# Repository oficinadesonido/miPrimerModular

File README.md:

# miPrimerModular
Archivos de construcción de módulos del proyecto Mi Primer Modular (My first modular)

Design & code: Daniel Llermaly
Graphic design: Joaquín Contreras
Typeface: contrafonts.cl

www.oficinadesonido.org
https://www.kickstarter.com/projects/oficinadesonido/my-first-modular

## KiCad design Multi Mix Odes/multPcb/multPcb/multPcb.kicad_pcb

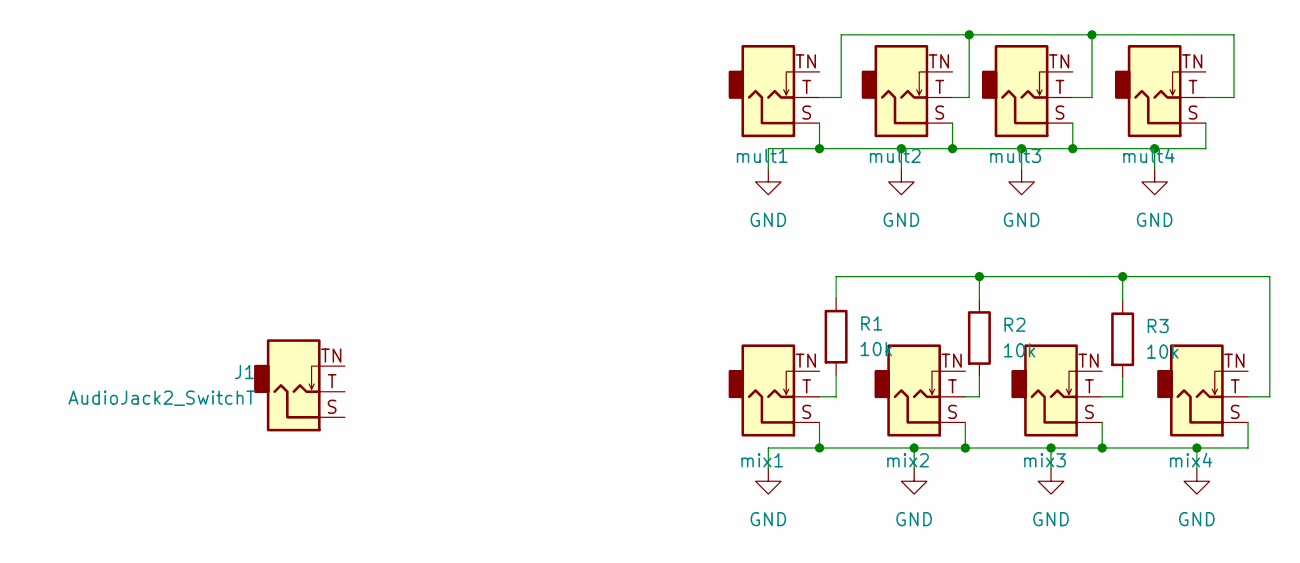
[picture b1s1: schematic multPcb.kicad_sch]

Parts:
J1: AudioJack2_SwitchT
R1, R2, R3: 10k; R_Axial_DIN0204_L3.6mm_D1.6mm_P1.90mm_Vertical
mix1, mix2, mix3, mix4: AudioJack2_Ground; jackEuroTSTN
mult1, mult2, mult3, mult4: AudioJack2_Ground; jackEuroTSTN

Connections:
GND: mix1.S, mix2.S, mix3.S, mix4.S, mult1.S, mult2.S, mult3.S, mult4.S
unnamed: R1.1, R2.1, R3.1, mix4.T
unnamed: R1.2, mix1.T
unnamed: R2.2, mix2.T
unnamed: R3.2, mix3.T
unnamed: mult1.T, mult2.T, mult3.T, mult4.T

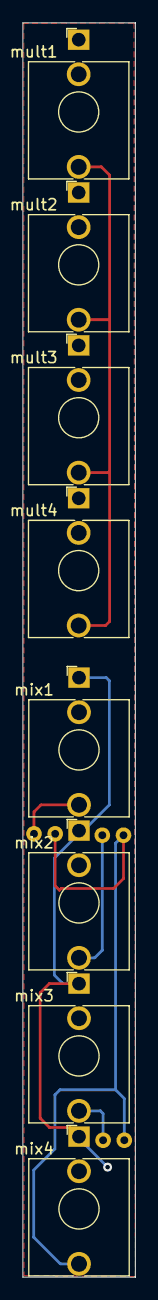
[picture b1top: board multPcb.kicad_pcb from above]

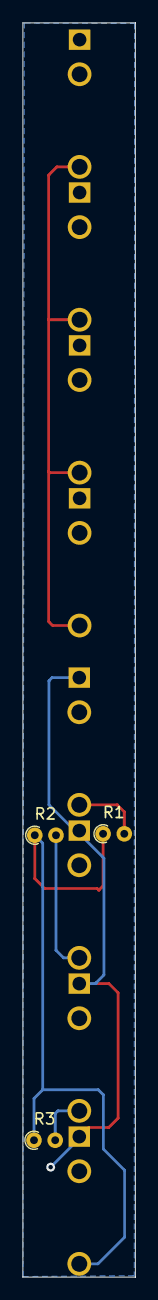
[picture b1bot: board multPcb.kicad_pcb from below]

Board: 2 copper layers, 10.1 x 112.4 mm, 11 parts (3 on the bottom side), 6 nets.

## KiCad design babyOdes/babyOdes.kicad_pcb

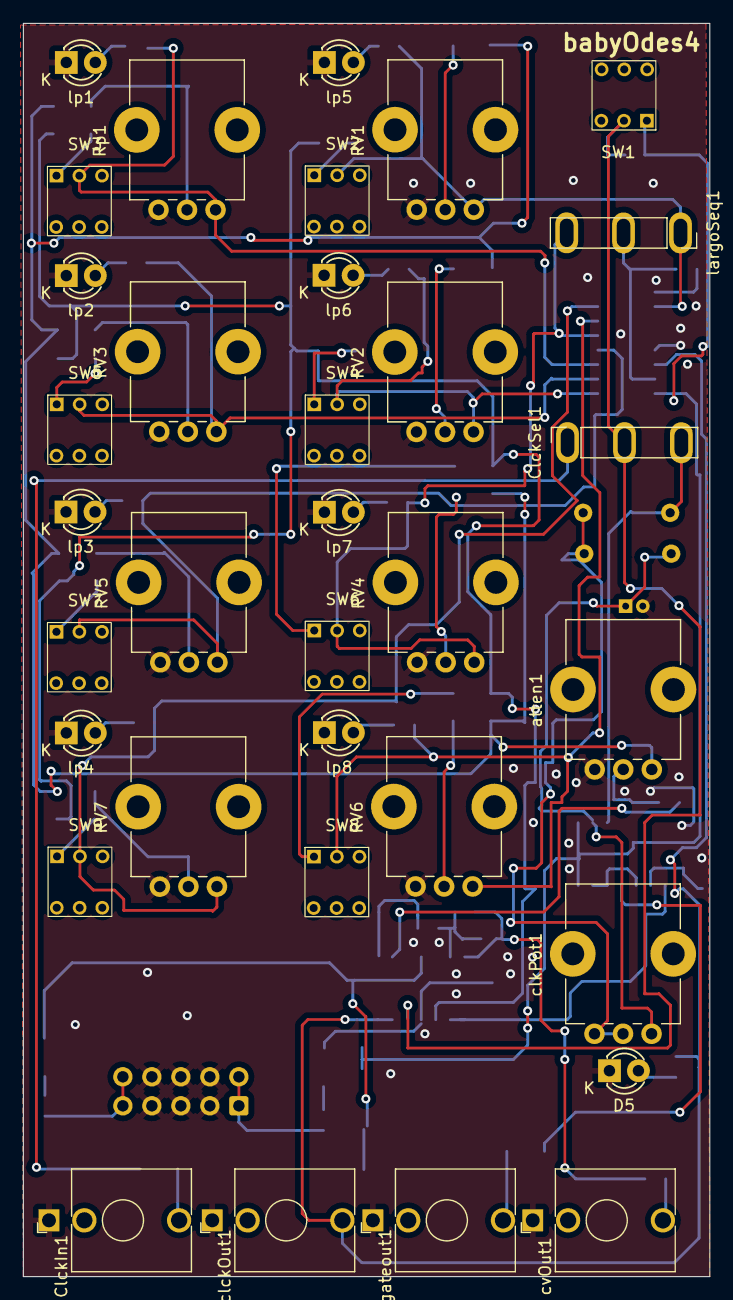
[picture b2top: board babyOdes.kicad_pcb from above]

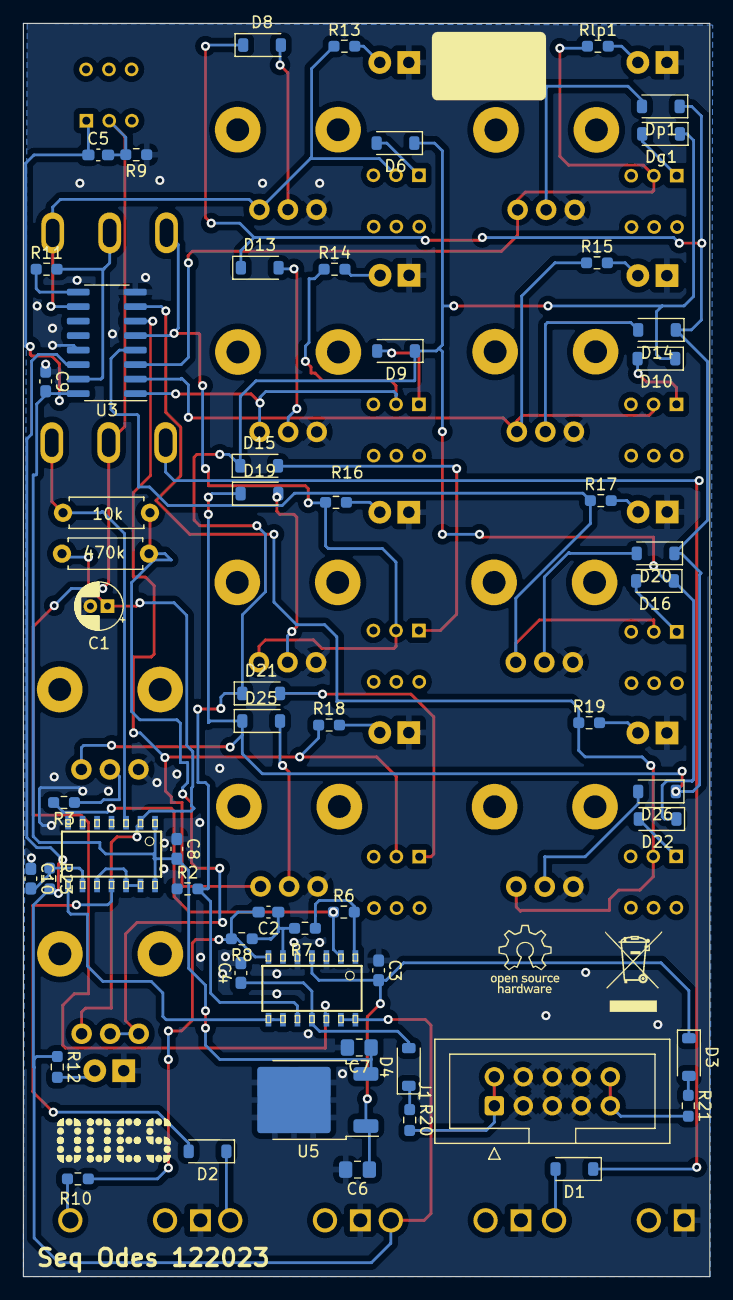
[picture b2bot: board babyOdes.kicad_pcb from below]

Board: 2 copper layers, 60.1 x 109.8 mm, 91 parts (57 on the bottom side), 63 nets.

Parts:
C1: 10uF; CP_Radial_D4.0mm_P1.50mm
C2: 470p; C_0603_1608Metric_Pad1.08x0.95mm_HandSolder
C3, C4, C5, C8, C9: 100nF; C_0603_1608Metric_Pad1.08x0.95mm_HandSolder
C6, C7: 1uF; C_0805_2012Metric_Pad1.18x1.45mm_HandSolder
C10: 0.1uF; C_0603_1608Metric_Pad1.08x0.95mm_HandSolder
ClckIn1: AudioJack2_SwitchT; jack3.5verticalTSTN
ClckSel1: SW_SPDT; colader
D1, D2: D; D_SOD-123
D3, D4, D6, D9, D10, D15, D16, D21, D22: D_Schottky; D_SOD-123
D5: LedClk; LED3mm
D8, D13, D14, D19, D20, D25, D26: 1N4148; D_SOD-123
Dg1: D_Schottky; D_SOD-123
Dp1: 1N4148; D_SOD-123
J1: Conn_02x05_Odd_Even; IDC-Header_2x05_P2.54mm_Vertical
R2, R3, R6, R7, R8, R9, R23: 100k; R_0603_1608Metric_Pad0.98x0.95mm_HandSolder
R4: 10k; R_Axial_DIN0207_L6.3mm_D2.5mm_P7.62mm_Horizontal
R10, R11: 1k; R_0603_1608Metric_Pad0.98x0.95mm_HandSolder
R12, R13, R14, R15, R16, R17, R18, R19: 10k; R_0603_1608Metric_Pad0.98x0.95mm_HandSolder
R20, R21: 10r; R_0603_1608Metric_Pad0.98x0.95mm_HandSolder
R22: 470k; R_Axial_DIN0207_L6.3mm_D2.5mm_P7.62mm_Horizontal
RV1, RV2, RV3, RV4, RV5, RV6, RV7: R_Potentiometer; PotGndPin1
Rlp1: 10k; R_0603_1608Metric_Pad0.98x0.95mm_HandSolder
Rp1: R_Potentiometer; PotGndPin1
SW1: SW_Push; SW_Push_5.8
SW2, SW3, SW4, SW5, SW6, SW7, SW8, SW9: SW_SPST; SW_Push_5.8
U1: HEF4093B; tl074
U2: TL074; tl074
U3: 4017; SOP-16_3.9x9.9mm_P1.27mm
U5: L7805; TO-252-2
atten1: 100k; PotGndPin1
clckOut1: AudioJack2_SwitchT; jack3.5verticalTSTN
clkPot1: 100k; PotGndPin1
cvOut1: AudioJack2_SwitchT; jack3.5verticalTSTN
gateout1: AudioJack2_SwitchT; jack3.5verticalTSTN
largoSeq1: SW_SPDT; colader
lp1, lp2, lp3, lp4, lp5, lp6, lp7, lp8: LED; LED3mm

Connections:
+5V: C5.1, C7.1, C8.2, C9.2, SW1.1, U1.1, U1.14 (VCC), U3.16 (VDD), U5.3 (OUT)
+12V: C3.2, C6.1, D3.1 (K), U2.4 (V+), U5.1 (IN)
-12V: C4.1, D4.2 (A), U2.11 (V-)
CV: D8.1 (K), D13.1 (K), D14.1 (K), D19.1 (K), D20.1 (K), D25.1 (K), D26.1 (K), Dp1.1 (K), atten1.3
GND: C1.2, C3.1, C4.2, C6.2, C7.2, C8.1, C9.1, C10.1, ClckIn1.S, D5.1 (K), J1.3, J1.4, J1.5, J1.6, J1.7, J1.8, R2.1, R9.1, RV1.1, RV2.1, RV3.1, RV4.1, RV5.1, RV6.1, RV7.1, Rp1.1, U1.7 (GND), U2.3 (+), U2.5 (+), U3.8 (VSS), U3.13 (CKEN), U5.2 (GND), atten1.1, clckOut1.S, cvOut1.S, gateout1.S, lp1.1 (K), lp2.1 (K), lp3.1 (K), lp4.1 (K), lp5.1 (K), lp6.1 (K), lp7.1 (K), lp8.1 (K)
Gate: D6.1 (K), D9.1 (K), D10.1 (K), D15.1 (K), D16.1 (K), D21.1 (K), D22.1 (K), Dg1.1 (K), R2.2, U2.10 (+)
unnamed: C1.1, R22.1, U1.2, clkPot1.3
unnamed: C2.2, R8.2, R10.1, U2.7
unnamed: C10.2, R23.1, U1.9
unnamed: ClckSel1.1 (A), D1.1 (K)
unnamed: C5.2, ClckSel1.2 (B), R9.2, SW1.2, U2.12 (+)
unnamed: ClckSel1.3 (C), R4.2, U1.3
unnamed: ClckIn1.T, D1.2 (A)
unnamed: D2.2 (A), U1.11
unnamed: D2.1 (K), gateout1.T
unnamed: D3.2 (A), R21.1
unnamed: D4.1 (K), R20.1
unnamed: D5.2 (A), R12.2
unnamed: D6.2 (A), SW2.1 (A)
unnamed: D8.2 (A), RV1.2
unnamed: D9.2 (A), SW4.1 (A)
unnamed: D10.2 (A), SW5.1 (A)
unnamed: D13.2 (A), RV2.2
unnamed: D14.2 (A), RV3.2
unnamed: D15.2 (A), SW6.1 (A)
unnamed: D16.2 (A), SW7.1 (A)
unnamed: D19.2 (A), RV4.2
unnamed: D20.2 (A), RV5.2
unnamed: D21.2 (A), SW8.1 (A)
unnamed: D22.2 (A), SW9.1 (A)
unnamed: D25.2 (A), RV6.2
unnamed: D26.2 (A), RV7.2
unnamed: Dg1.2 (A), SW3.1 (A)
unnamed: Dp1.2 (A), Rp1.2
unnamed: J1.1, J1.2, R20.2
unnamed: J1.9, J1.10, R21.2
unnamed: R3.1, atten1.2
unnamed: R6.2, R7.1, U2.1
unnamed: R10.2, cvOut1.T
unnamed: R4.1, R22.2, clkPot1.1, clkPot1.2
unnamed: U1.10, U1.12, U1.13
unnamed: R3.2, R6.1, U2.2 (-)
unnamed: C2.1, R7.2, R8.1, U2.6 (-)
unnamed: R11.2, U3.15 (Reset), largoSeq1.2 (B)
unnamed: Rlp1.2, lp1.2 (A)
unnamed: R15.2, lp2.2 (A)
unnamed: R17.2, lp3.2 (A)
unnamed: R19.2, lp4.2 (A)
unnamed: R13.2, lp5.2 (A)
unnamed: R14.2, lp6.2 (A)
unnamed: R16.2, lp7.2 (A)
unnamed: R18.2, lp8.2 (A)
clk: R12.1, R23.2, U2.13 (-), U2.14, U3.14 (CLK), clckOut1.T
gateAmp: U1.8, U2.8, U2.9 (-)
paso0: Rlp1.1, Rp1.3, SW3.2 (B), U3.3 (Q0)
paso1: R15.1, RV3.3, SW5.2 (B), U3.2 (Q1)
paso2: R17.1, RV5.3, SW7.2 (B), U3.4 (Q2)
paso3: R19.1, RV7.3, SW9.2 (B), U3.7 (Q3)
paso4: R13.1, RV1.3, SW2.2 (B), U3.10 (Q4), largoSeq1.1 (A)
paso5: R14.1, RV2.3, SW4.2 (B), U3.1 (Q5)
paso6: R16.1, RV4.3, SW6.2 (B), U3.5 (Q6), largoSeq1.3 (C)
paso7: R18.1, RV6.3, SW8.2 (B), U3.6 (Q7)
paso8: R11.1, U3.9 (Q8)

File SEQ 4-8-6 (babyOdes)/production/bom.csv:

Designator,Footprint,Quantity,Value,LCSC Part #
C1,CP_Radial_D4.0mm_P1.50mm,1,10uF,
C10,0603,1,0.1uF,
C2,0603,1,470p,
"C3, C4, C5, C8, C9",0603,5,100nF,
"C6, C7",0805,2,1uF,
"ClckIn1, clckOut1, cvOut1, gateout1",jack3.5verticalTSTN,4,AudioJack2_SwitchT,
"ClckSel1, largoSeq1",colader,2,SW_SPDT,
"D1, D2",D_SOD-123,2,D,
"D10, D15, D16, D21, D22, D3, D4, D6, D9, Dg1",D_SOD-123,10,D_Schottky,
"D13, D14, D19, D20, D25, D26, D8, Dp1",D_SOD-123,8,1N4148,
D5,LED3mm,1,LedClk,
J1,IDC-Header_2x05_P2.54mm_Vertical,1,Conn_02x05_Odd_Even,
"R10, R11",0603,2,1k,
"R12, R13, R14, R15, R16, R17, R18, R19, Rlp1",0603,9,10k,
"R2, R23, R3, R6, R7, R8, R9",0603,7,100k,
"R20, R21",0603,2,10r,
R22,R_Axial_DIN0207_L6.3mm_D2.5mm_P7.62mm_Horizontal,1,470k,
R4,R_Axial_DIN0207_L6.3mm_D2.5mm_P7.62mm_Horizontal,1,10k,
"RV1, RV2, RV3, RV4, RV5, RV6, RV7, Rp1",PotGndPin1,8,R_Potentiometer,
SW1,SW_Push_5.8,1,SW_Push,
"SW2, SW3, SW4, SW5, SW6, SW7, SW8, SW9",SW_Push_5.8,8,SW_SPST,
U1,tl074,1,HEF4093B,
U2,tl074,1,TL074,
U3,SOP-16_3.9x9.9mm_P1.27mm,1,4017,
U5,TO-252-2,1,L7805,C310413
"atten1, clkPot1",PotGndPin1,2,100k,
"lp1, lp2, lp3, lp4, lp5, lp6, lp7, lp8",LED3mm,8,LED,

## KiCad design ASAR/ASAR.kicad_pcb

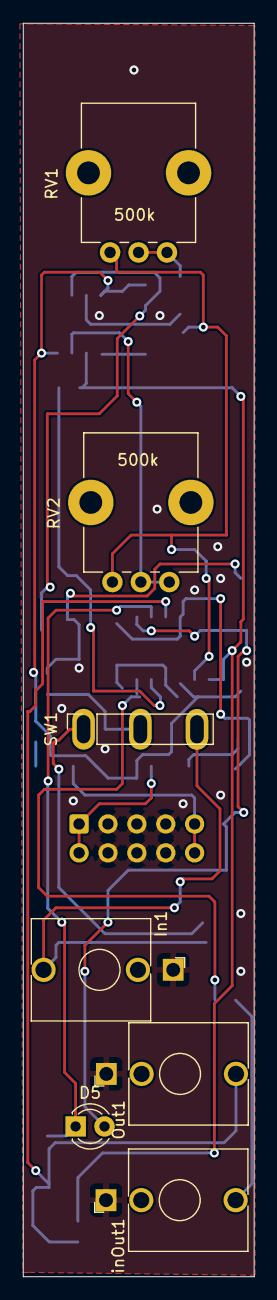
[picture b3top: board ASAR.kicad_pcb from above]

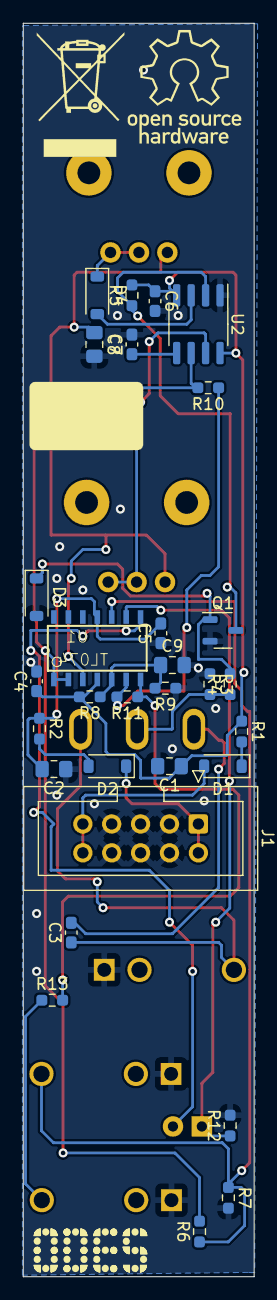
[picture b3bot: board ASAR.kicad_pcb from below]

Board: 2 copper layers, 20.3 x 110.2 mm, 37 parts (30 on the bottom side), 25 nets.

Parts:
C1, C2: 10uF; C_0805_2012Metric_Pad1.18x1.45mm_HandSolder
C3: 100pf; C_0603_1608Metric_Pad1.08x0.95mm_HandSolder
C4, C5, C6: 100nF; C_0603_1608Metric_Pad1.08x0.95mm_HandSolder
C7: 0.01uf; C_0603_1608Metric_Pad1.08x0.95mm_HandSolder
C8: 4.7uF; C_0805_2012Metric_Pad1.18x1.45mm_HandSolder
C9: 1uF; C_0805_2012Metric_Pad1.18x1.45mm_HandSolder
D1, D2: D; D_SOD-123
D3, D4: 1N4148; D_SOD-123
D5: LED; LED_D3.0mm_Clear
In1: Audio-Jack-3; jack3.5vertical
J1: Power Input; IDC-Header_2x05_P2.54mm_Vertical
Out1: Audio-Jack-3; jack3.5vertical
Q1: MMBT3904; SOT-23-3
R1, R2: 10r; R_0603_1608Metric_Pad0.98x0.95mm_HandSolder
R3, R4: 100k; R_0603_1608Metric_Pad0.98x0.95mm_HandSolder
R5, R8, R11: 10k; R_0603_1608Metric_Pad0.98x0.95mm_HandSolder
R6: 2k; R_0603_1608Metric_Pad0.98x0.95mm_HandSolder
R7: 3.3k; R_0603_1608Metric_Pad0.98x0.95mm_HandSolder
R9: 4.7k; R_0603_1608Metric_Pad0.98x0.95mm_HandSolder
R10: 15k; R_0603_1608Metric_Pad0.98x0.95mm_HandSolder
R12, R13: 1k; R_0603_1608Metric_Pad0.98x0.95mm_HandSolder
RV1, RV2: 500k; PotGndPin1
SW1: SW_SPDT; colader
U1: TL074; SOP-14
U2: LM555xN; SOP-8_3.76x4.96mm_P1.27mm
inOut1: Audio-Jack-3; jack3.5vertical

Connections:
+12V: C1.1, C4.1, C6.1, R1.1, R5.2, R8.2, U1.4 (V+), U2.4 (R), U2.8 (VCC)
-12V: C2.2, C5.2, R2.1, U1.11 (V-)
GND: C1.2, C2.1, C4.2, C5.1, C6.2, C7.2, C8.2, C9.2, D3.2 (A), In1.3, J1.3, J1.4, J1.5, J1.6, J1.7, J1.8, Out1.3, Q1.2 (E), R3.1, R7.2, R9.1, R12.2, U2.1 (GND), inOut1.3
unnamed: D1.2 (A), J1.9, J1.10
unnamed: D1.1 (K), R1.2
unnamed: D2.2 (A), R2.2
unnamed: D2.1 (K), J1.1, J1.2
unnamed: D3.1 (K), Q1.1 (B), R4.2
unnamed: D4.2 (A), U2.3 (Q)
unnamed: D4.1 (K), RV1.2, RV1.3
unnamed: D5.2 (A), U1.8
unnamed: D5.1 (K), R12.1, U1.9 (-)
unnamed: Q1.3 (C), R5.1, U2.2 (TR)
unnamed: R11.1, R13.2, U1.7
unnamed: R13.1, inOut1.1
unnamed: C3.2, SW1.1 (A)
unnamed: R3.2, R4.1, SW1.2 (B)
unnamed: C3.1, In1.1, SW1.3 (C)
unnamed: C8.1, RV1.1, RV2.1, U1.3 (+)
unnamed: R6.2, R10.2, U1.1, U1.2 (-), U2.6 (THR)
unnamed: C9.1, R8.1, R9.2, U1.5 (+)
unnamed: R10.1, R11.2, U1.6 (-)
unnamed: Out1.1, R6.1, R7.1, U1.10 (+)
unnamed: C7.1, U2.5 (CV)
unnamed: RV2.2, RV2.3, U2.7 (DIS)

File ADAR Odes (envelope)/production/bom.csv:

Designator,Footprint,Quantity,Value,LCSC Part #
"C1, C2",0805,2,10uF,
C3,0603,1,100pf,
"C4, C5, C6",0603,3,100nF,
C7,0603,1,0.01uf,
C8,0805,1,4.7uF,
C9,0805,1,1uF,
"D1, D2",D_SOD-123,2,D,
"D3, D4",D_SOD-123,2,1N4148,
D5,LED_D3.0mm_Clear,1,LED,
"In1, Out1, inOut1",jack3.5vertical,3,Audio-Jack-3,
J1,IDC-Header_2x05_P2.54mm_Vertical,1,Power Input,
Q1,SOT-23-3,1,MMBT3904,
"R1, R2",0603,2,10r,
R10,0603,1,15k,
"R11, R5, R8",0603,3,10k,
"R12, R13",0603,2,1k,
"R3, R4",0603,2,100k,
R6,0603,1,2k,
R7,0603,1,3.3k,
R9,0603,1,4.7k,
"RV1, RV2",PotGndPin1,2,500k,
SW1,colader,1,SW_SPDT,
U1,SOP-14,1,TL074,
U2,SOP-8_3.76x4.96mm_P1.27mm,1,LM555xN,

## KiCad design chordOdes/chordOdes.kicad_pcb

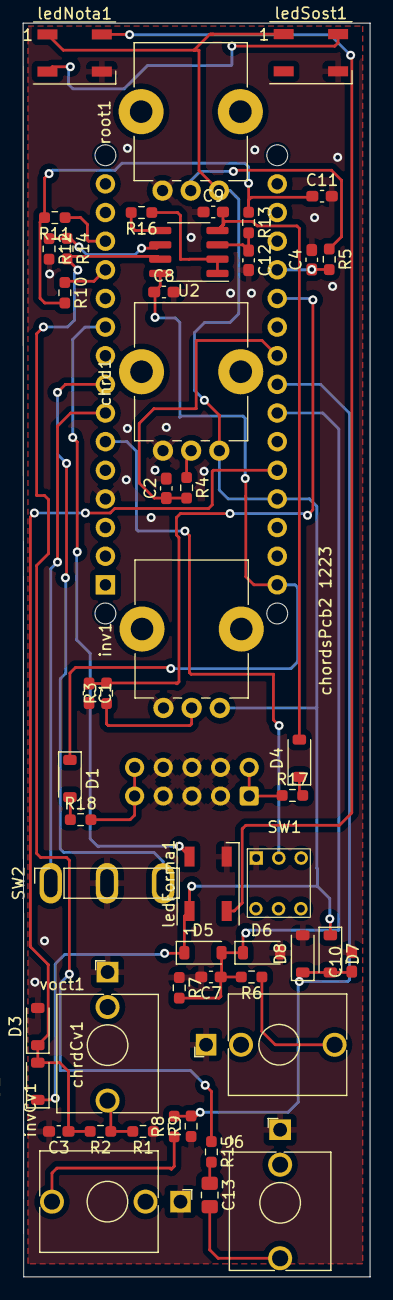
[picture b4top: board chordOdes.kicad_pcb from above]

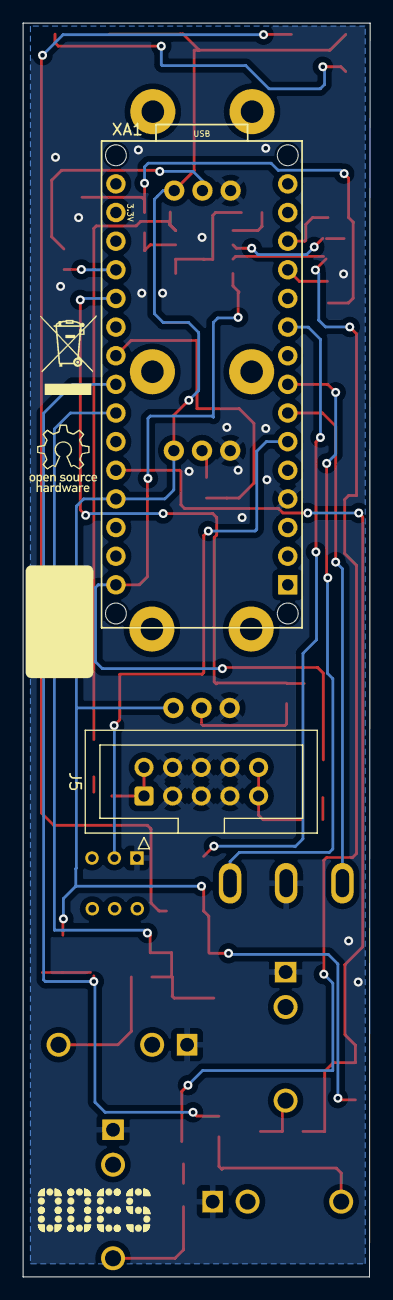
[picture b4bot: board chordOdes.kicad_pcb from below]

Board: 2 copper layers, 30.8 x 111.2 mm, 52 parts (2 on the bottom side), 36 nets.

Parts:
C1, C2, C4, C8, C9, C12: 10nF; C_0603_1608Metric_Pad1.08x0.95mm_HandSolder
C3, C7, C10: 68nF; C_0603_1608Metric_Pad1.08x0.95mm_HandSolder
C11: 4.7nF; C_0603_1608Metric_Pad1.08x0.95mm_HandSolder
C13: 4.7uF; C_0805_2012Metric_Pad1.18x1.45mm_HandSolder
D1, D4: D; D_SOD-123
D2, D3, D5, D6, D7, D8: D_Schottky; D_SOD-123
J5: Conn_02x05_Odd_Even; IDC-Header_2x05_P2.54mm_Vertical
J6: AudioJack2_Ground; jackEuroTSTN
R1, R7, R9: 100k; R_0603_1608Metric_Pad0.98x0.95mm_HandSolder
R2: 100r; R_0603_1608Metric_Pad0.98x0.95mm_HandSolder
R3, R4, R5, R6, R8, R12, R14, R16: 1k; R_0603_1608Metric_Pad0.98x0.95mm_HandSolder
R10, R13: 3.9k; R_0603_1608Metric_Pad0.98x0.95mm_HandSolder
R11: 499k; R_0603_1608Metric_Pad0.98x0.95mm_HandSolder
R15: 220r; R_0603_1608Metric_Pad0.98x0.95mm_HandSolder
R17, R18: 10r; R_0603_1608Metric_Pad0.98x0.95mm_HandSolder
SW1: SW_Push; SW_Push_5.8
SW2: SW_SPDT; colader
U2: TL072; SOP-8_3.76x4.96mm_P1.27mm
XA1: Arduino_Nano_Socket
chrd1: R_Potentiometer; PotGndPin1
chrdCv1: AudioJack2_Ground; jackEuroTSTN
inv1: R_Potentiometer; PotGndPin1
invCv1: AudioJack2_Ground; jackEuroTSTN
ledForma1: NeoPixel_THT; LED_WS2812B
ledNota1: NeoPixel_THT; LED_WS2812B
ledSost1: NeoPixel_THT; LED_WS2812B
root1: R_Potentiometer; PotGndPin1
voct1: AudioJack2_Ground; jackEuroTSTN

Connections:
+5V: D2.1 (K), D5.1 (K), D7.1 (K), XA1.5V, chrd1.3, inv1.3, ledForma1.3 (VDD), ledNota1.3 (VDD), ledSost1.3 (VDD), root1.3
-12V: C9.2, D4.2 (A), U2.4 (V-)
GND: C1.2, C2.2, C3.2, C4.2, C7.2, C8.2, C9.1, C10.2, C11.2, C12.2, D3.2 (A), D6.2 (A), D8.2 (A), J5.3, J5.4, J5.5, J5.6, J5.7, J5.8, J6.G, R1.1, R7.1, R9.1, R12.2, SW1.1, SW2.2 (B), XA1.GND1 (GND), chrd1.1, chrdCv1.G, inv1.1, invCv1.G, ledForma1.2 (GND), ledNota1.2 (GND), ledSost1.2 (GND), root1.1, voct1.G
unnamed: C11.1, R10.2, R11.2, R13.1
unnamed: C13.1, R15.2
unnamed: D1.2 (A), R18.1
unnamed: D4.1 (K), R17.2
unnamed: J5.1, J5.2, R17.1
unnamed: J5.9, J5.10, R18.2
unnamed: R1.2, R2.1, voct1.T
unnamed: R3.1, inv1.2
unnamed: R4.1, chrd1.2
unnamed: R5.1, root1.2
unnamed: R6.1, chrdCv1.T
unnamed: R8.1, invCv1.T
unnamed: R10.1, XA1.D9
unnamed: R14.2, R15.1, U2.7
unnamed: R16.1, U2.1, U2.2 (-)
unnamed: R16.2, U2.5 (+)
unnamed: R12.1, R14.1, U2.6 (-)
unnamed: R11.1, XA1.D10 (D10_CS)
unnamed: ledForma1.1 (DOUT), ledNota1.4 (DIN)
unnamed: ledNota1.1 (DOUT), ledSost1.4 (DIN)
btnFrm: SW1.2, XA1.D3 (D3_INT1)
chrd: C2.1, R4.2, XA1.A3
chrdCv: C7.1, D5.2 (A), D6.1 (K), R6.2, R7.2, XA1.A5 (A5_SCL)
inv: C1.1, R3.2, XA1.A1
invCv: C10.1, D7.2 (A), D8.1 (K), R8.2, R9.2, XA1.A4 (A4_SDA)
led: XA1.D7, ledForma1.4 (DIN)
modeSw1: SW2.1 (A), XA1.D4
modeSw2: SW2.3 (C), XA1.D5
out: C13.2, J6.T
preOut: C12.1, R13.2, U2.3 (+)
root: C4.1, R5.2, XA1.A0
vin: C8.1, D1.1 (K), U2.8 (V+), XA1.VIN
voct: C3.1, D2.2 (A), D3.1 (K), R2.2, XA1.A7

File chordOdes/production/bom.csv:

Designator,Footprint,Quantity,Value,LCSC Part #
"C1, C12, C2, C4, C8, C9",0603,6,10nF,
"C10, C3, C7",0603,3,68nF,
C11,0603,1,4.7nF,
C13,0805,1,4.7uF,
"D1, D4",D_SOD-123,2,D,
"D2, D3, D5, D6, D7, D8",D_SOD-123,6,D_Schottky,
J5,IDC-Header_2x05_P2.54mm_Vertical,1,Conn_02x05_Odd_Even,
"J6, chrdCv1, invCv1, voct1",jackEuroTSTN,4,AudioJack2_Ground,
"R1, R7, R9",0603,3,100k,
"R10, R13",0603,2,3.9k,
R11,0603,1,499k,
"R12, R14, R16, R3, R4, R5, R6, R8",0603,8,1k,
R15,0603,1,220r,
"R17, R18",0603,2,10r,
R2,0603,1,100r,
SW1,SW_Push_5.8,1,SW_Push,
SW2,colader,1,SW_SPDT,
U2,SOP-8_3.76x4.96mm_P1.27mm,1,TL072,
XA1,Arduino_Nano_Socket,1,Arduino_Nano_Socket,
"chrd1, inv1, root1",PotGndPin1,3,R_Potentiometer,
"ledForma1, ledNota1, ledSost1",LED_WS2812B,3,NeoPixel_THT,

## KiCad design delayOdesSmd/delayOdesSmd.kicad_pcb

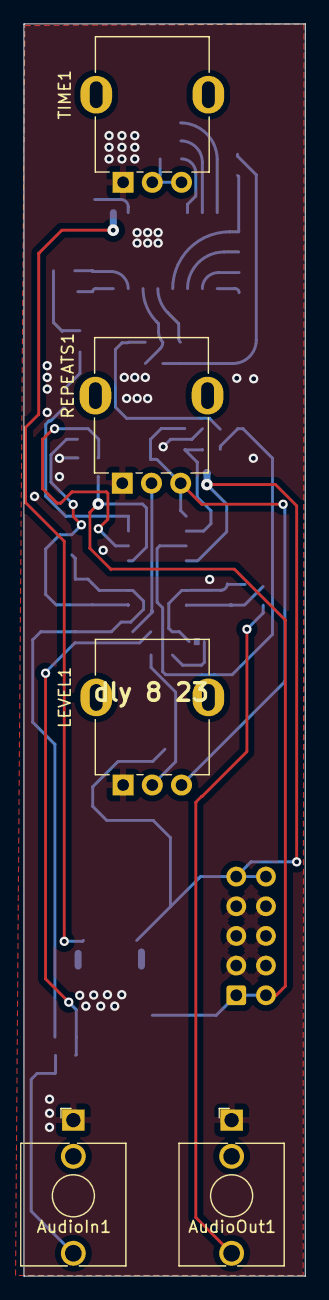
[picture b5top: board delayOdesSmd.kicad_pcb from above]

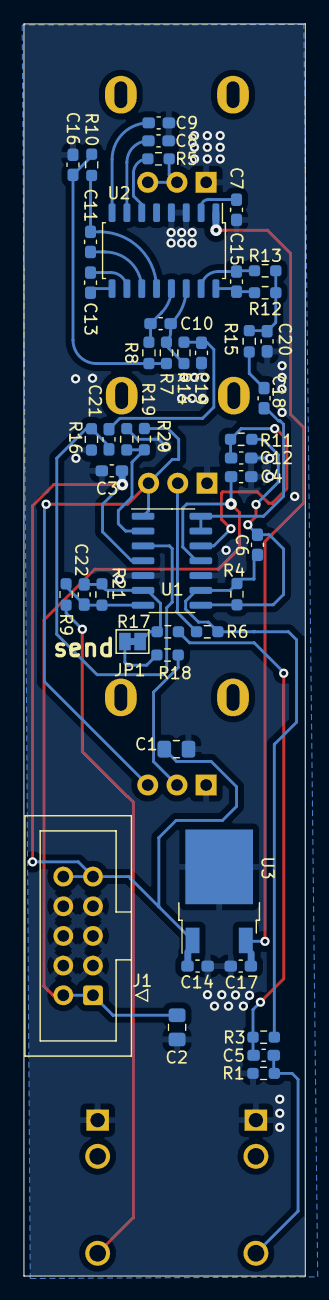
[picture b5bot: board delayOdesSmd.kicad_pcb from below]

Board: 2 copper layers, 24.1 x 107.2 mm, 52 parts (47 on the bottom side), 36 nets.

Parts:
AudioIn1: AudioJack2_SwitchT; AudioJack_3.5mm
AudioOut1: AudioJack2_SwitchT; AudioJack_3.5mm
C1, C2: 22uF; C_0805_2012Metric_Pad1.18x1.45mm_HandSolder
C3, C4, C8, C9, C11, C13, C17: 100nF; C_0603_1608Metric_Pad1.08x0.95mm_HandSolder
C5: 220nF; C_0603_1608Metric_Pad1.08x0.95mm_HandSolder
C6: 47pF; C_0603_1608Metric_Pad1.08x0.95mm_HandSolder
C7, C18: 1uF; C_0603_1608Metric_Pad1.08x0.95mm_HandSolder
C10, C12, C15, C19: 2.2nF; C_0603_1608Metric_Pad1.08x0.95mm_HandSolder
C14: 330nF; C_0603_1608Metric_Pad1.08x0.95mm_HandSolder
C16: 15nF; C_0603_1608Metric_Pad1.08x0.95mm_HandSolder
C20: 4.7nF; C_0603_1608Metric_Pad1.08x0.95mm_HandSolder
C21: 10nF; C_0603_1608Metric_Pad1.08x0.95mm_HandSolder
C22: 68pF; C_0603_1608Metric_Pad1.08x0.95mm_HandSolder
J1: IDC_2x05; IDC-Header_2x05_P2.54mm_Vertical
JP1: Jumper_2_Bridged; SolderJumper-2_P1.3mm_Bridged_Pad1.0x1.5mm
LEVEL1: B10k; Potentiometer_RV09
R1, R16: 1M; R_0603_1608Metric_Pad0.98x0.95mm_HandSolder
R3, R6, R17, R20, R21: 100k; R_0603_1608Metric_Pad0.98x0.95mm_HandSolder
R4, R8, R10, R11, R12, R13, R14, R15: 10k; R_0603_1608Metric_Pad0.98x0.95mm_HandSolder
R5: 2.7k; R_0603_1608Metric_Pad0.98x0.95mm_HandSolder
R7, R19: 20k; R_0603_1608Metric_Pad0.98x0.95mm_HandSolder
R9: 1k; R_0603_1608Metric_Pad0.98x0.95mm_HandSolder
R18: 68k; R_0603_1608Metric_Pad0.98x0.95mm_HandSolder
REPEATS1: B10k; Potentiometer_RV09
TIME1: B100k; Potentiometer_RV09
U1: TL074; SOIC-14_3.9x8.7mm_P1.27mm
U2: PT2399; SOP-16_4.55x10.3mm_P1.27mm
U3: L7805; TO-252-2

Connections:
+5V: C17.1, U2.1 (VCC), U3.3 (OUT)
+12V: C1.1, C3.1, C14.1, J1.9, J1.10, U1.4 (V+), U3.1 (IN)
-12V: C2.2, C4.2, J1.1, J1.2, U1.11 (V-)
DRY_OUT: C5.1, R3.1, R17.1
GND: AudioIn1.S, AudioOut1.S, C1.2, C2.1, C3.2, C4.1, C7.2, C8.1, C9.1, C12.1, C14.2, C16.1, C17.2, C19.1, C20.2, J1.3, J1.4, J1.5, J1.6, J1.7, J1.8, LEVEL1.1, R1.1, R16.1, R19.1, REPEATS1.1, TIME1.1, U1.5 (+), U1.10 (+), U2.3 (AGND), U2.4 (DGND), U3.2 (GND)
unnamed: AudioIn1.T, C5.2, R1.2
unnamed: AudioOut1.T, R9.1
unnamed: C6.1, R4.2, R11.1, U1.8
unnamed: C16.2, R7.1, R8.1, R10.1
unnamed: C18.1, R15.1
unnamed: C19.2, C21.1, R14.1
unnamed: C20.1, R12.1, R13.1, R15.2
unnamed: C22.1, R9.2, R21.2, U1.7
unnamed: JP1.1 (A), R18.2
unnamed: C22.2, JP1.2 (B), R17.2, R21.1, U1.6 (-)
unnamed: LEVEL1.3, R20.2, REPEATS1.3, U1.1
unnamed: R5.2, TIME1.2, TIME1.3
unnamed: C21.2, R16.2, U1.3 (+)
unnamed: R19.2, R20.1, U1.2 (-)
unnamed: C6.2, R3.2, R4.1, R6.2, U1.9 (-)
unnamed: C12.2, R11.2, U1.12 (+)
unnamed: C18.2, U1.13 (-), U1.14
unnamed: C9.2, U2.8 (CC0)
unnamed: C8.2, U2.7 (CC1)
unnamed: C15.2, R12.2, U2.16 (LPF1-IN)
unnamed: C15.1, R13.2, U2.15 (LPF1-OUT)
unnamed: C10.1, R8.2, U2.13 (LPF2-IN)
unnamed: C10.2, R7.2, R14.2, U2.14 (LPF2-OUT)
unnamed: C13.2, U2.10 (OP1-IN)
unnamed: C13.1, U2.9 (OP1-OUT)
unnamed: C11.1, U2.11 (OP2-IN)
unnamed: C11.2, R10.2, U2.12 (OP2-OUT)
unnamed: C7.1, U2.2 (REF)
unnamed: R5.1, U2.6 (VCO)
REPEATS: R6.1, REPEATS1.2
WET_OUT: LEVEL1.2, R18.1

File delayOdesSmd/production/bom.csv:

Designator,Footprint,Quantity,Value,LCSC Part #
"AudioIn1, AudioOut1",AudioJack_3.5mm,2,AudioJack2_SwitchT,
"C1, C2",0805,2,22uF,C49678
"C10, C12, C15, C19",0603,4,2.2nF,C107043
"C11, C13, C17, C3, C4, C8, C9",0603,7,100nF,C91183
C14,0603,1,330nF,C107070
C16,0603,1,15nF,C2210963
"C18, C7",0603,2,1uF,C105174
C20,0603,1,4.7nF,C115060
C21,0603,1,10nF,C115056
C22,0603,1,68pF,C519457
C5,0603,1,220nF,C97857
C6,0603,1,47pF,C105622
"D2, D3",D_SOD-123,2,1N4001,
J1,IDC-Header_2x05_P2.54mm_Vertical,1,IDC_2x05,C706914
JP1,SolderJumper-2_P1.3mm_Bridged_Pad1.0x1.5mm,1,Jumper_2_Bridged,
"LEVEL1, REPEATS1",Potentiometer_RV09,2,B10k,
"R1, R16",0603,2,1M,C105578
"R10, R11, R12, R13, R14, R15, R4, R8",0603,8,10k,C116677
"R17, R20, R21, R3, R6",0603,5,100k,C14675
R18,0603,1,68k,C114633
"R19, R7",0603,2,20k,C105575
"R22, R23",0603,2,10r,C116677
R5,0603,1,2.7k,C114612
R9,0603,1,1k,C22548
TIME1,Potentiometer_RV09,1,B100k,
U1,SOIC-14_3.9x8.7mm_P1.27mm,1,TL074,C107644
U2,SOP-16_4.55x10.3mm_P1.27mm,1,PT2399,C126407
U3,TO-252-2,1,L7805,C310413

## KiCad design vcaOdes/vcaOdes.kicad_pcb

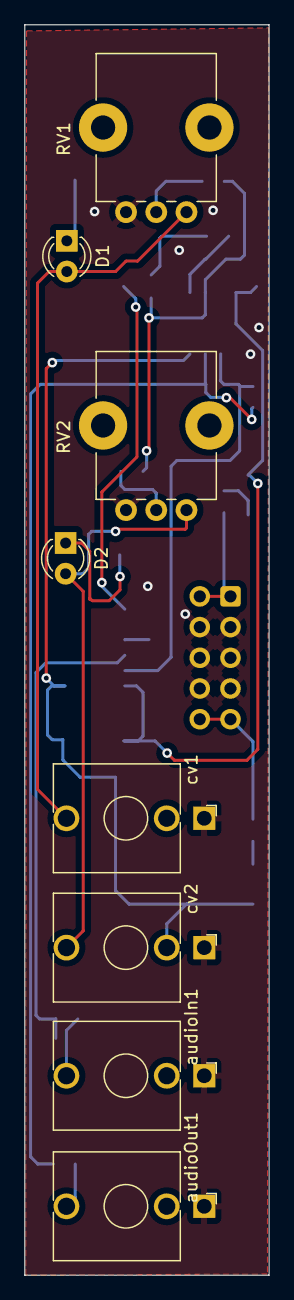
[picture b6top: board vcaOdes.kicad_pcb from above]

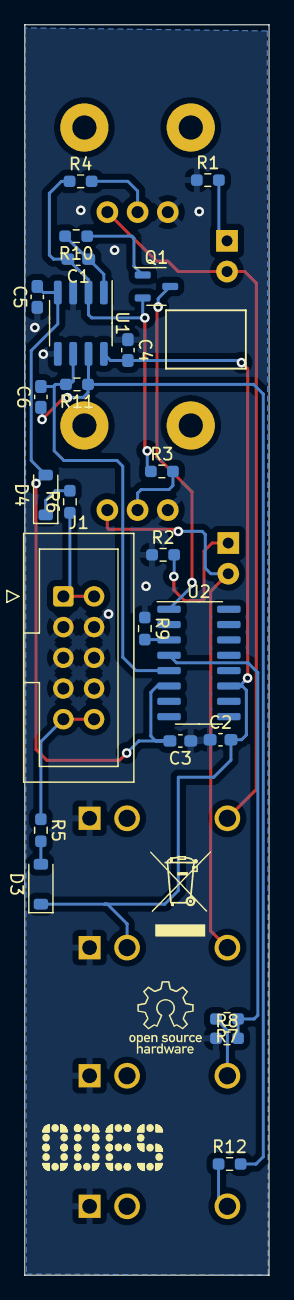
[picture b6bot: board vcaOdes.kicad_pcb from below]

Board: 2 copper layers, 20.2 x 103.4 mm, 32 parts (24 on the bottom side), 23 nets.

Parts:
C1, C6: 120pF; C_0603_1608Metric_Pad1.08x0.95mm_HandSolder
C2, C3, C4, C5: 100nF; C_0603_1608Metric_Pad1.08x0.95mm_HandSolder
D1, D2: LED; LED_D3.0mm
D3, D4: 1N4001; D_SOD-123
J1: Conn_02x05_Odd_Even; IDC-Header_2x05_P2.54mm_Vertical
Q1: BC559; SOT-23-BEC
R1, R2: 10k; R_0603_1608Metric_Pad0.98x0.95mm_HandSolder
R3, R4, R7, R10: 20k; R_0603_1608Metric_Pad0.98x0.95mm_HandSolder
R5, R6: 10r; R_0603_1608Metric_Pad0.98x0.95mm_HandSolder
R8, R9: 100; R_0603_1608Metric_Pad0.98x0.95mm_HandSolder
R11: 47k; R_0603_1608Metric_Pad0.98x0.95mm_HandSolder
R12: 680; R_0603_1608Metric_Pad0.98x0.95mm_HandSolder
RV1, RV2: 100k; Pot-bourns-alpha
U1: TL072; SOP-8_3.76x4.96mm_P1.27mm
U2: LM13700; SOIC-16_3.9x9.9mm_P1.27mm
audioIn1: AudioJack2_SwitchT; jackEuroTSTN
audioOut1: AudioJack2_SwitchT; jackEuroTSTN
cv1, cv2: AudioJack2_SwitchT; jackEuroTSTN

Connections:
+12V: C2.2, C4.2, D3.1 (K), U1.8 (V+), U2.11 (V+), cv2.TN
-12V: C3.2, C5.2, D4.2 (A), U1.4 (V-), U2.6 (V-)
GND: C2.1, C3.1, C4.1, C5.1, J1.3, J1.4, J1.5, J1.6, J1.7, J1.8, R1.1, R2.1, R8.1, R9.1, RV1.3, RV2.3, U1.3 (+), U1.5 (+), audioIn1.S, audioOut1.S, cv1.S, cv2.S
unnamed: C1.1, R10.2, U1.1
unnamed: C6.1, R11.1, R12.2, U1.7
unnamed: D1.2 (A), RV1.1, cv1.T
unnamed: D1.1 (K), R1.2
unnamed: D2.2 (A), RV2.1, cv2.T
unnamed: D2.1 (K), R2.2
unnamed: D3.2 (A), R5.2
unnamed: D4.1 (K), R6.2
unnamed: J1.1, J1.2, R6.1
unnamed: J1.9, J1.10, R5.1
unnamed: Q1.2 (B), R10.1
unnamed: Q1.1 (C), U2.1
unnamed: C1.2, Q1.3 (E), R3.1, R4.1, U1.2 (-)
unnamed: R3.2, RV2.2
unnamed: R4.2, RV1.2
unnamed: R7.2, audioIn1.T
unnamed: R12.1, audioOut1.T
unnamed: C6.2, R11.2, U1.6 (-), U2.5
unnamed: R9.2, U2.3 (+)
unnamed: R7.1, R8.2, U2.4 (-)

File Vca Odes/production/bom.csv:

Designator,Footprint,Quantity,Value,LCSC Part #
"C1, C6",0603,2,120pF,
"C2, C3, C4, C5",0603,4,100nF,
"D1, D2",LED_D3.0mm,2,LED,
"D3, D4",D_SOD-123,2,1N4001,
J1,IDC-Header_2x05_P2.54mm_Vertical,1,Conn_02x05_Odd_Even,
Q1,SOT-23-BEC,1,BC559,
"R1, R2",0603,2,10k,
"R10, R3, R4, R7",0603,4,20k,
R11,0603,1,47k,
R12,0603,1,680,
"R5, R6",0603,2,10r,
"R8, R9",0603,2,100,
"RV1, RV2",Pot-bourns-alpha,2,100k,
U1,SOP-8_3.76x4.96mm_P1.27mm,1,TL072,
U2,SOIC-16_3.9x9.9mm_P1.27mm,1,LM13700,
"audioIn1, audioOut1, cv1, cv2",jackEuroTSTN,4,AudioJack2_SwitchT,

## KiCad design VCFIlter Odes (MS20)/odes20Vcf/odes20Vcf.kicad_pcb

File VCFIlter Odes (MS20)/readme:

This is an VCF Low Pass and Hi Pass Filter MS-20 style. Part of the My First Modular Project by http://oficinadesonido.org

Adaptation made by Daniel Llermaly
Art Panel by @jkocontreras

Based on Simple ms20_vcf Arthur Saunier (https://github.com/arthursaunier/Synth/tree/main/ms20_vcf/simple)
which is based on Michael Barton's work (https://www.bartonmusicalcircuits.com/synthstuff.html#analog)

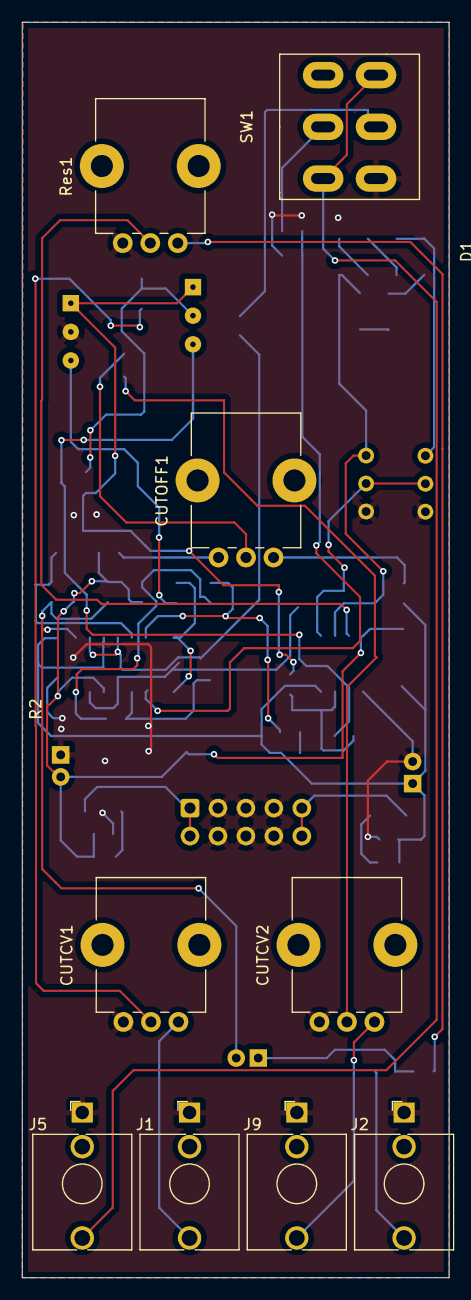
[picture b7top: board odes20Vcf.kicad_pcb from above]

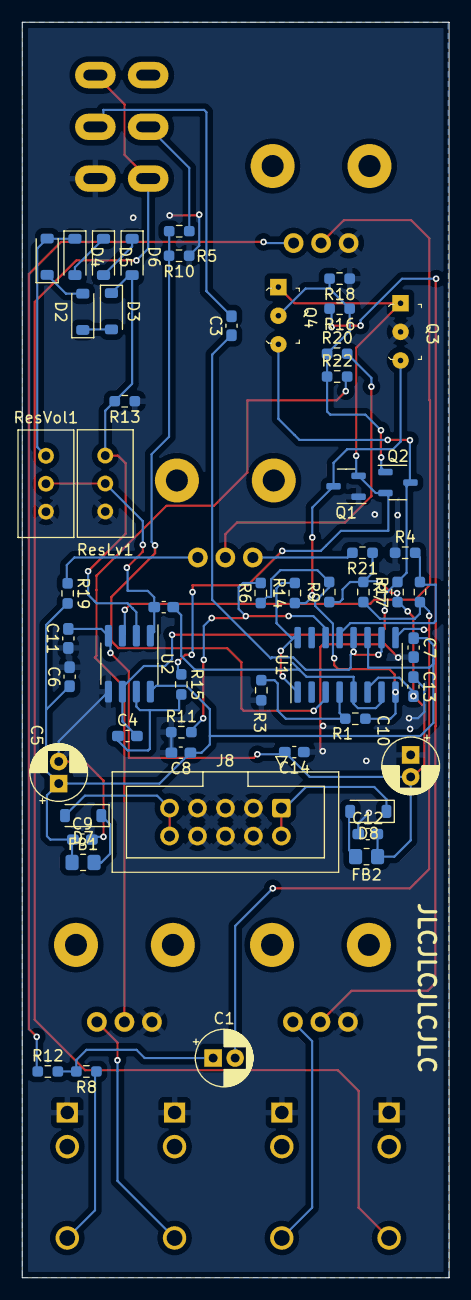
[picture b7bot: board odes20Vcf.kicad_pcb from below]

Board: 2 copper layers, 38.8 x 114.1 mm, 64 parts (55 on the bottom side), 42 nets.

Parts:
C1, C5, C10: 10uF; CP_Radial_D5.0mm_P2.00mm
C2, C3, C4: 1nF; C_0603_1608Metric_Pad1.08x0.95mm_HandSolder
C6, C7, C8, C9, C11, C12, C13, C14: 100nF; C_0603_1608Metric_Pad1.08x0.95mm_HandSolder
CUTCV1, CUTCV2: 100k; Pot-bourns-alpha
CUTOFF1: 100k; Pot-bourns-alpha
D1, D2, D3, D4, D5, D6: 1N4148; D_SOD-123
D7, D8: D; D_SOD-123
FB1, FB2: 10R; R_0805_2012Metric_Pad1.20x1.40mm_HandSolder
J1, J9: FilterCV1; Thonkiconn
J2: FilterOut1; Thonkiconn
J5: FilterIn1; Thonkiconn
J8: Power Input; IDC-Header_2x05_P2.54mm_Vertical
Q1, Q2: BC559; SOT-23-BEC
Q3, Q4: BC559; BC548tht
R1, R2, R5, R6, R17, R20: 100k; R_0603_1608Metric_Pad0.98x0.95mm_HandSolder
R3, R4, R10, R11: 470; R_0603_1608Metric_Pad0.98x0.95mm_HandSolder
R7, R9: 1.8k; R_0603_1608Metric_Pad0.98x0.95mm_HandSolder
R8, R12, R15: 1k; R_0603_1608Metric_Pad0.98x0.95mm_HandSolder
R13, R14, R18: 2.2k; R_0603_1608Metric_Pad0.98x0.95mm_HandSolder
R16, R22: 82k; R_0603_1608Metric_Pad0.98x0.95mm_HandSolder
R19: 33k; R_0603_1608Metric_Pad0.98x0.95mm_HandSolder
R21: 56k; R_0603_1608Metric_Pad0.98x0.95mm_HandSolder
Res1: 100k; Pot-bourns-alpha
ResLv1: 10k; Potentiometer_Bourns_3386C_Horizontal
ResVol1: 10k; Potentiometer_Bourns_3386C_Horizontal
SW1: Hpass/Lpass Switch; SW_DPDT_Toggle
U1: LM13700; SOIC-16_3.9x9.9mm_P1.27mm
U2: TL072; SOP-8_3.76x4.96mm_P1.27mm

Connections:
+12V: C5.1, C6.1, C7.1, C8.1, C9.1, FB1.1, R19.2, U1.11 (V+), U2.8 (V+)
-12V: C10.2, C11.2, C12.2, C13.2, C14.2, FB2.1, R7.1, R9.1, R17.1, R21.1, U1.6 (V-), U2.4 (V-)
/CVIn: CUTCV1.1, J1.T
/CVIn2: CUTCV2.1, J9.T
/Cutoff: Q2.2 (B), Q4.2 (B), R16.1, R18.2, R20.1, R22.1
/FilterIn: J5.T, SW1.3 (C), SW1.4 (A)
/FilterOut: J2.T, R8.1
/HPass: C3.2, SW1.5 (B)
/LPass: R5.1, SW1.2 (B)
/Out1: C1.1, R8.2, R12.2
/ResOut: Res1.2, U2.3 (+)
GND: C5.2, C6.2, C7.2, C8.2, C9.2, C10.1, C11.1, C12.1, C13.1, C14.1, CUTCV1.3, CUTCV2.3, J1.S, J2.S, J5.S, J8.3, J8.4, J8.5, J8.6, J8.7, J8.8, J9.S, Q1.2 (B), Q3.2 (B), R3.1, R4.1, R10.1, R11.1, R13.1, R18.1, Res1.3, ResLv1.1, ResVol1.3, SW1.6 (C), U2.5 (+)
unnamed: C1.2, R2.2, R7.2, U1.9
unnamed: C2.1, U1.5, U1.7
unnamed: C2.2, ResLv1.2, ResVol1.2, U2.1
unnamed: C3.1, U1.10, U1.12
unnamed: C4.1, R15.2, U2.7
unnamed: CUTCV1.2, R16.2
unnamed: CUTCV2.2, R22.2
unnamed: CUTOFF1.1, R19.1
unnamed: CUTOFF1.2, R20.2
unnamed: CUTOFF1.3, R21.2
unnamed: D1.2 (A), D4.1 (K), ResVol1.1
unnamed: D1.1 (K), D2.2 (A)
unnamed: D2.1 (K), D3.2 (A)
unnamed: D3.1 (K), D6.2 (A), R13.2, ResLv1.3, U2.2 (-)
unnamed: D4.2 (A), D5.1 (K)
unnamed: D5.2 (A), D6.1 (K)
unnamed: D7.2 (A), J8.9, J8.10
unnamed: D7.1 (K), FB1.2
unnamed: D8.2 (A), FB2.2
unnamed: D8.1 (K), J8.1, J8.2
unnamed: Q1.1 (C), Q3.1 (C), R14.1
unnamed: Q1.3 (E), Q2.3 (E), Q3.3 (E), Q4.3 (E), R15.1
unnamed: C4.2, Q2.1 (C), Q4.1 (C), R17.2, U2.6 (-)
unnamed: R1.2, R6.1, R9.2, U1.8
unnamed: R12.1, Res1.1
unnamed: R14.2, U1.1, U1.16
unnamed: R6.2, R11.2, U1.14 (+)
unnamed: R2.1, R4.2, U1.13 (-)
unnamed: R5.2, R10.2, U1.3 (+)
unnamed: R1.1, R3.2, U1.4 (-)
